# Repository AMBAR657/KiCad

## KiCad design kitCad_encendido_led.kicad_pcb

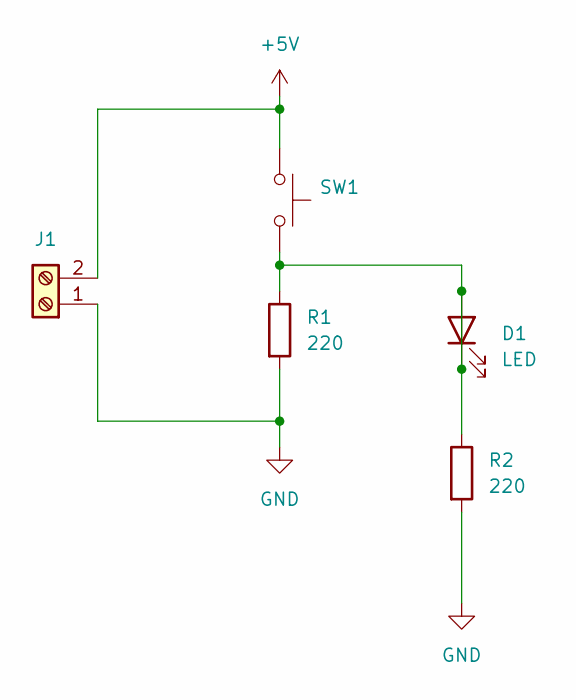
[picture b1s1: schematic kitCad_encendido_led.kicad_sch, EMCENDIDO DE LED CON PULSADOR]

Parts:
D1: LED; LED_D5.0mm
J1: Screw_Terminal_01x02; TerminalBlock_bornier-2_P5.08mm
R1, R2: 220; R_Axial_DIN0411_L9.9mm_D3.6mm_P20.32mm_Horizontal
SW1: SW_Push; SW_PUSH_6mm

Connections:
+5V: J1.2, SW1.1
GND: J1.1, R1.2, R2.2
unnamed: D1.1 (K), D1.2 (A), R1.1, R2.1, SW1.2

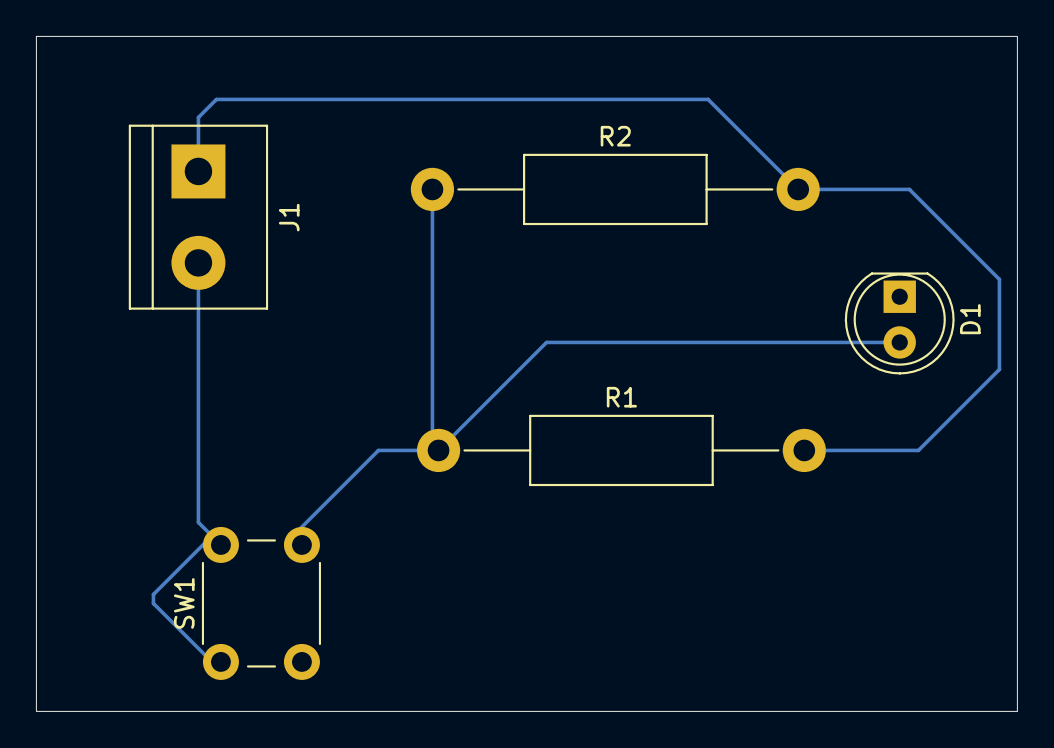
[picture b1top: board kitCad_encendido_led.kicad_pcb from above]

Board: 2 copper layers, 54.5 x 37.5 mm, 5 parts (0 on the bottom side), 3 nets.

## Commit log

2024-11-04 Encendido de leds
